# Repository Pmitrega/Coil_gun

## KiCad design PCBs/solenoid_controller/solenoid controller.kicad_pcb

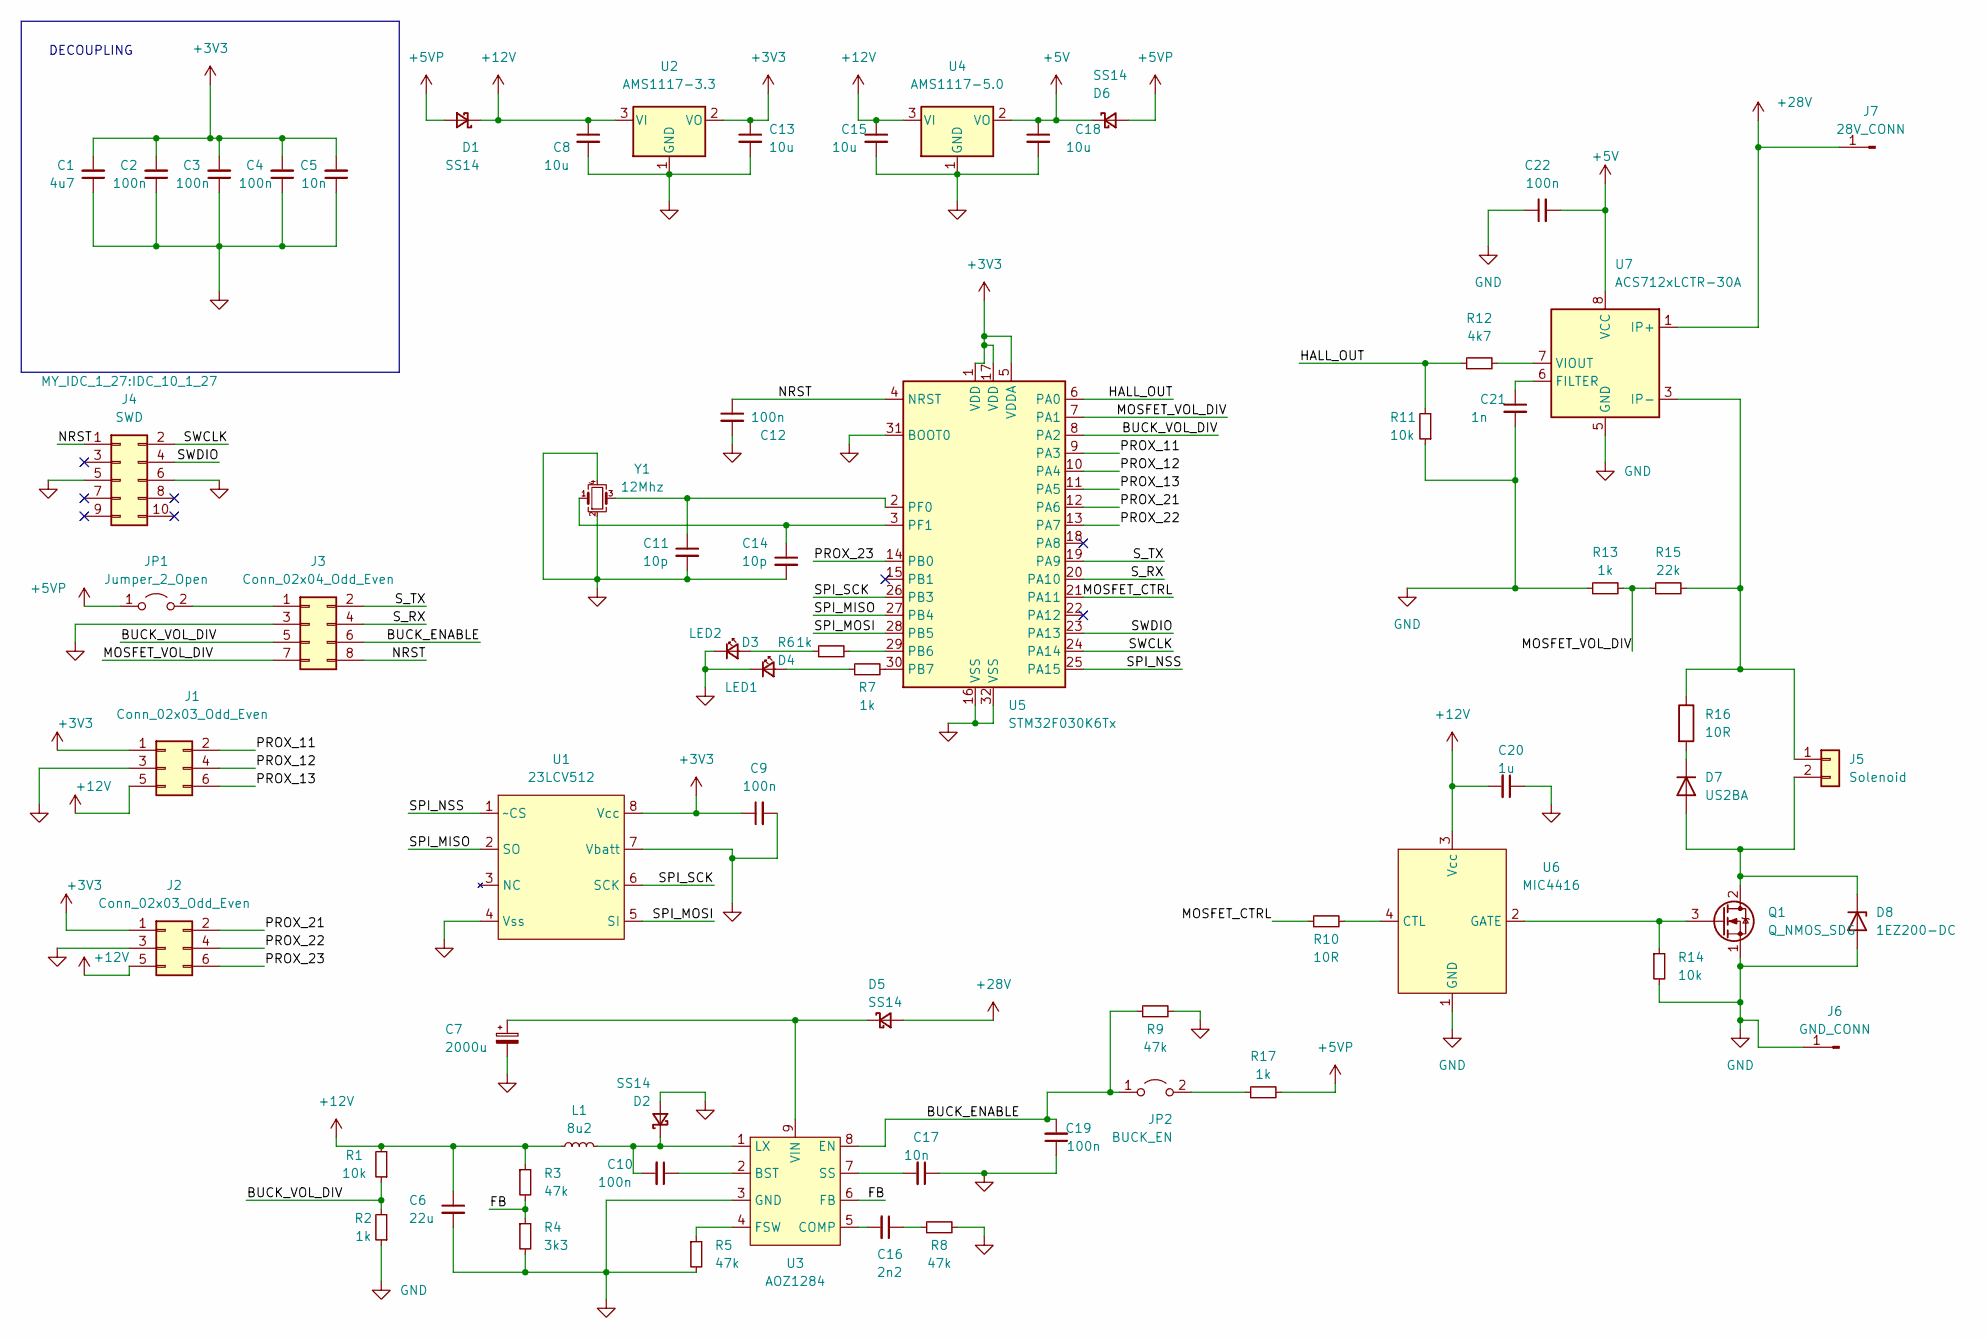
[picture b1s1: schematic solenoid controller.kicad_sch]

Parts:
C1: 4u7; C_0603_1608Metric_Pad1.08x0.95mm_HandSolder
C2, C3, C4, C9, C10, C12, C19, C22: 100n; C_0603_1608Metric_Pad1.08x0.95mm_HandSolder
C5, C17: 10n; C_0603_1608Metric_Pad1.08x0.95mm_HandSolder
C6: 22u; C_0805_2012Metric_Pad1.18x1.45mm_HandSolder
C7: 2000u; CP_Radial_D8.0mm_P3.50mm
C8, C13, C15, C18: 10u; C_0805_2012Metric_Pad1.18x1.45mm_HandSolder
C11, C14: 10p; C_0603_1608Metric_Pad1.08x0.95mm_HandSolder
C16: 2n2; C_0603_1608Metric_Pad1.08x0.95mm_HandSolder
C20: 1u; C_0603_1608Metric_Pad1.08x0.95mm_HandSolder
C21: 1n; C_0603_1608Metric_Pad1.08x0.95mm_HandSolder
D1, D2, D5, D6: SS14; D_SMA_Handsoldering
D3: LED2; LED_0603_1608Metric_Pad1.05x0.95mm_HandSolder
D4: LED1; LED_0603_1608Metric_Pad1.05x0.95mm_HandSolder
D7: US2BA; D_SMA_Handsoldering
D8: 1EZ200-DC; D_DO-41_SOD81_P12.70mm_Horizontal
J1, J2: Conn_02x03_Odd_Even; IDC-Header_2x03_P2.54mm_Vertical
J3: Conn_02x04_Odd_Even; IDC-Header_2x04_P2.54mm_Vertical
J4: SWD; IDC_10_1_27
J5: Solenoid; L_Bourns_SRR1208_12.7x12.7mm
J6: GND_CONN; single_PAD
J7: 28V_CONN; single_PAD
JP1: Jumper_2_Open; PinHeader_1x02_P2.54mm_Vertical
JP2: BUCK_EN; PinHeader_1x02_P2.54mm_Vertical
L1: 8u2; L_7.3x7.3_H4.5
Q1: Q_NMOS_SDG; TO-263-2
R1, R11, R14: 10k; R_0603_1608Metric_Pad0.98x0.95mm_HandSolder
R2, R6, R7, R13, R17: 1k; R_0603_1608Metric_Pad0.98x0.95mm_HandSolder
R3, R5, R8, R9: 47k; R_0603_1608Metric_Pad0.98x0.95mm_HandSolder
R4: 3k3; R_0603_1608Metric_Pad0.98x0.95mm_HandSolder
R10: 10R; R_0603_1608Metric_Pad0.98x0.95mm_HandSolder
R12: 4k7; R_0603_1608Metric_Pad0.98x0.95mm_HandSolder
R15: 22k; R_0603_1608Metric_Pad0.98x0.95mm_HandSolder
R16: 10R; R_2512_6332Metric_Pad1.40x3.35mm_HandSolder
U1: 23LCV512; SO-8_5.3x6.2mm_P1.27mm
U2: AMS1117-3.3; SOT-223-3_TabPin2
U3: AOZ1284; SO-8-pad
U4: AMS1117-5.0; SOT-223-3_TabPin2
U5: STM32F030K6Tx; LQFP-32_7x7mm_P0.8mm
U6: MIC4416; SOT-143_Handsoldering
U7: ACS712xLCTR-30A; SOIC-8_3.9x4.9mm_P1.27mm
Y1: 12Mhz; Crystal_SMD_3225-4Pin_3.2x2.5mm_HandSoldering

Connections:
+3V3: C1.2, C2.2, C3.2, C4.2, C5.2, C9.1, C13.1, J1.1, J2.1, U1.8 (Vcc), U2.2 (VO), U5.1 (VDD), U5.5 (VDDA), U5.17 (VDD)
+5V: C18.1, C22.2, D6.1 (K), U4.2 (VO), U7.8 (VCC)
+5VP: D1.2 (A), D6.2 (A), JP1.1 (A), R17.2
+12V: C6.1, C8.1, C15.1, C20.2, D1.1 (K), J1.5, J2.5, L1.1, R1.2, R3.1, U2.3 (VI), U4.3 (VI), U6.3 (Vcc)
+28V: D5.2 (A), J7.1, U7.1 (IP+), U7.2 (IP+)
/BUCK_ENABLE: C19.2, J3.6, JP2.1 (A), R9.1, U3.8 (EN)
/BUCK_VOL_DIV: J3.5, R1.1, R2.2, U5.8 (PA2)
/FB: R3.2, R4.1, U3.6 (FB)
/HALL_OUT: R11.2, R12.1, U5.6 (PA0)
/MOSFET_CTRL: R10.1, U5.21 (PA11)
/MOSFET_VOL_DIV: J3.7, R13.2, R15.1, U5.7 (PA1)
/NRST: C12.1, J3.8, J4.1, U5.4 (NRST); also elsewhere on the board
/PROX_11: J1.2, U5.9 (PA3)
/PROX_12: J1.4, U5.10 (PA4)
/PROX_13: J1.6, U5.11 (PA5)
/PROX_21: J2.2, U5.12 (PA6)
/PROX_22: J2.4, U5.13 (PA7)
/PROX_23: J2.6, U5.14 (PB0)
/SPI_MISO: U1.2 (SO), U5.27 (PB4)
/SPI_MOSI: U1.5 (SI), U5.28 (PB5)
/SPI_NSS: U1.1 (~CS), U5.25 (PA15)
/SPI_SCK: U1.6 (SCK), U5.26 (PB3)
/SWCLK: J4.2, U5.24 (PA14)
/SWDIO: J4.4, U5.23 (PA13)
/S_RX: J3.4, U5.20 (PA10)
/S_TX: J3.2, U5.19 (PA9)
GND: C1.1, C2.1, C3.1, C4.1, C5.1, C6.2, C7.2, C8.2, C9.2, C11.2, C12.2, C13.2, C14.2, C15.2, C17.1, C18.2, C19.1, C20.1, C21.2, C22.1, D2.2 (A), D3.1 (K), D4.1 (K), D8.2 (A), J1.3, J2.3, J3.3, J4.5, J4.6, J6.1, Q1.1 (S), R2.1, R4.2, R5.2, R8.2, R9.2, R11.1, R13.1, R14.2, U1.4 (Vss), U1.7 (Vbatt), U2.1 (GND), U3.3 (GND), U4.1 (GND), U5.16 (VSS), U5.31 (BOOT0), U5.32 (VSS), U6.1 (GND), U7.5 (GND), Y1.2, Y1.4; also elsewhere on the board
unnamed: C16.1, R8.1
unnamed: C10.2, D2.1 (K), L1.2, U3.1 (LX)
unnamed: D3.2 (A), R6.1
unnamed: D4.2 (A), R7.1
unnamed: C7.1, D5.1 (K), U3.9 (VIN)
unnamed 32: D7.2 (A), D8.1 (K), J5.2, Q1.2 (D); also elsewhere on the board
unnamed: D7.1 (K), R16.2
unnamed: J3.1, JP1.2 (B)
unnamed: J5.1, R15.2, R16.1, U7.3 (IP-), U7.4 (IP-)
unnamed: JP2.2 (B), R17.1
unnamed 37: Q1.3 (G), R14.1, U6.2 (GATE); also elsewhere on the board
unnamed: C10.1, U3.2 (BST)
unnamed: C16.2, U3.5 (COMP)
unnamed: R5.1, U3.4 (FSW)
unnamed: C17.2, U3.7 (SS)
unnamed: R6.2, U5.29 (PB6)
unnamed: R7.2, U5.30 (PB7)
unnamed: C11.1, U5.2 (PF0), Y1.3
unnamed: C14.1, U5.3 (PF1), Y1.1
unnamed: R10.2, U6.4 (CTL)
unnamed: C21.1, U7.6 (FILTER)
unnamed: R12.2, U7.7 (VIOUT)

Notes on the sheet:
DECOUPLING

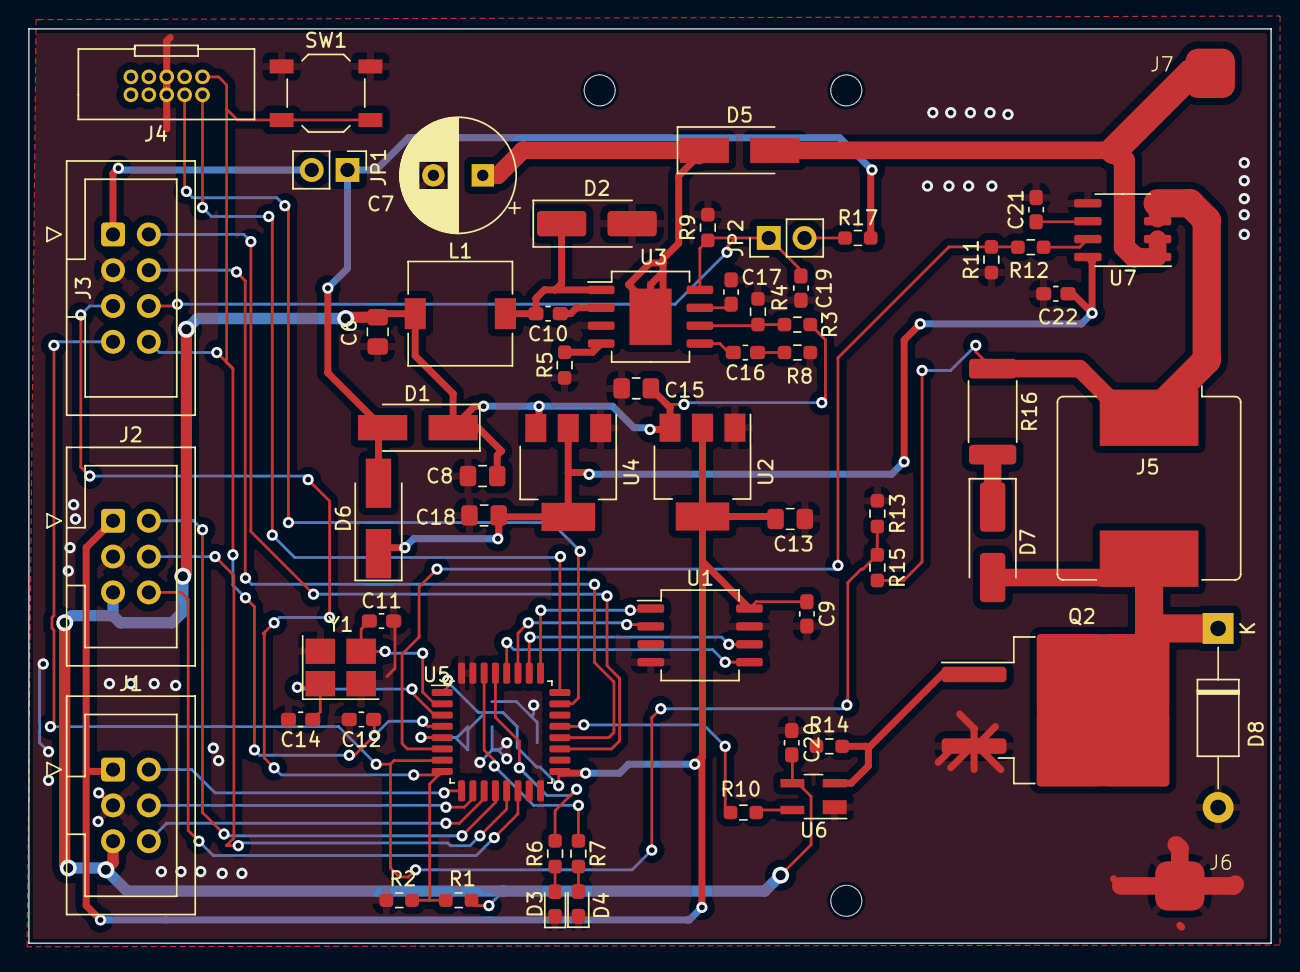
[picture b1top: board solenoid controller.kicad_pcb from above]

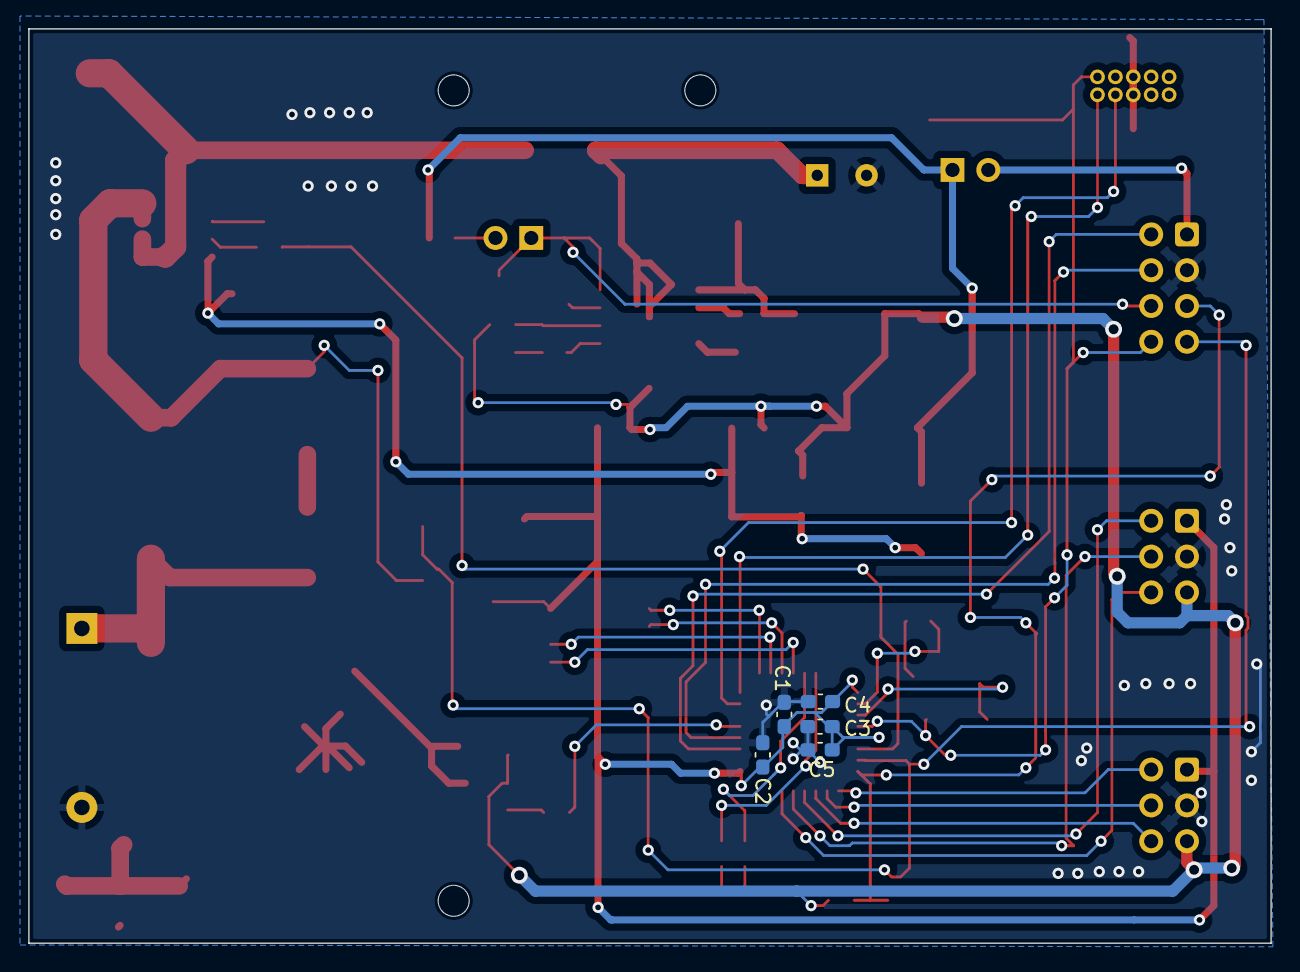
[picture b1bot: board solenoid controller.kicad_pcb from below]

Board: 2 copper layers, 88.1 x 64.9 mm, 67 parts (5 on the bottom side), 49 nets.

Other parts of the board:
Q2: Q_NMOS_GDS; TO-263-2
SW1: SW_Push; SW_SPST_TL3342

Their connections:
/NRST: SW1.2; also elsewhere on the board
GND: Q2.3 (S), SW1.1; also elsewhere on the board
unnamed 32: Q2.2 (D); also elsewhere on the board
unnamed 37: Q2.1 (G); also elsewhere on the board

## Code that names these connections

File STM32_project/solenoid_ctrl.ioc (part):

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Mcu.Name=STM32F030K6Tx
Mcu.Package=LQFP32
Mcu.UserName=STM32F030K6Tx
PA0.GPIOParameters=GPIO_Label
PA0.GPIO_Label=HALL_V
PA0.Mode=IN0
PA0.Signal=ADC_IN0
PA1.GPIOParameters=GPIO_Label
PA1.GPIO_Label=MOS_V
PA1.Mode=IN1
PA1.Signal=ADC_IN1
PA10.Mode=Asynchronous
PA10.Signal=USART1_RX
PA11.Signal=GPIO_Output
PA13.Mode=Serial_Wire
PA13.Signal=SYS_SWDIO
PA14.Mode=Serial_Wire
PA14.Signal=SYS_SWCLK
PA15.Mode=NSS_Signal_Hard_Output
PA15.Signal=SPI1_NSS
PA2.GPIOParameters=GPIO_Label
PA2.GPIO_Label=BUCK_V
PA2.Mode=IN2
PA2.Signal=ADC_IN2
PA3.GPIOParameters=GPIO_Label
PA3.GPIO_Label=PROX_11
PA3.Mode=IN3
PA3.Signal=ADC_IN3
PA4.GPIOParameters=GPIO_Label
PA4.GPIO_Label=PROX_12
PA4.Mode=IN4
PA4.Signal=ADC_IN4
PA5.GPIOParameters=GPIO_Label
PA5.GPIO_Label=PROX_13
PA5.Mode=IN5
PA5.Signal=ADC_IN5
PA6.GPIOParameters=GPIO_Label
PA6.GPIO_Label=PROX_21
PA6.Mode=IN6
PA6.Signal=ADC_IN6
PA7.GPIOParameters=GPIO_Label
PA7.GPIO_Label=PROX_22
PA7.Mode=IN7
PA7.Signal=ADC_IN7
PA9.Mode=Asynchronous
PA9.Signal=USART1_TX
PB0.GPIOParameters=GPIO_Label
PB0.GPIO_Label=PROX_23
PB0.Mode=IN8
PB0.Signal=ADC_IN8
PB1.Mode=IN9
PB1.Signal=ADC_IN9
PB3.Mode=Full_Duplex_Master
PB3.Signal=SPI1_SCK
PB4.Mode=Full_Duplex_Master
PB4.Signal=SPI1_MISO
PB5.Mode=Full_Duplex_Master
PB5.Signal=SPI1_MOSI
PB6.GPIOParameters=GPIO_Label
PB6.GPIO_Label=LED2
PB6.Signal=GPIO_Output
PB7.GPIOParameters=GPIO_Label
PB7.GPIO_Label=LED1
PB7.Signal=GPIO_Output
PF0-OSC_IN.Mode=HSE-External-Oscillator
PF0-OSC_IN.Signal=RCC_OSC_IN
PF1-OSC_OUT.Mode=HSE-External-Oscillator
PF1-OSC_OUT.Signal=RCC_OSC_OUT
board=custom

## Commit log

2023-12-25 Initial commit with design concept
2023-12-31 circuitry in progress + cubemx project for stm32
2024-01-13 PCB update
2024-01-15 solenoid controller finished
